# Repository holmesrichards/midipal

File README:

Midipal, the MIDI swiss army knife.

A midi in, a midi out, a small display, an encoder ; 20 awesome features:

* MIDI monitor
* BPM counter
* Keyboard splitter
* Note dispatcher / voice stealing / polyphonic driver
* Channels merger
* Channel filter
* Clock divider
* Clock source, with swing
* CC and NRPN knob
* 8 pots/sensors voltage reader/controller
* Drum pattern generator (including Euclidian patterns)
* Note, velocity and CC randomizer
* Chord memory
* Arpeggiator
* Sequencer
* CC lfo
* Tempo-synchronized note delay (with transposition and decay velocity)
* Slave start/stop synchronizer (à la Mungo Sync)
* Scale processor / harmonizer
* Ear training game

Forked from pichenettes' version and identical except:
- Eagle brd and sch files converted to XML (making possible import into KiCad)

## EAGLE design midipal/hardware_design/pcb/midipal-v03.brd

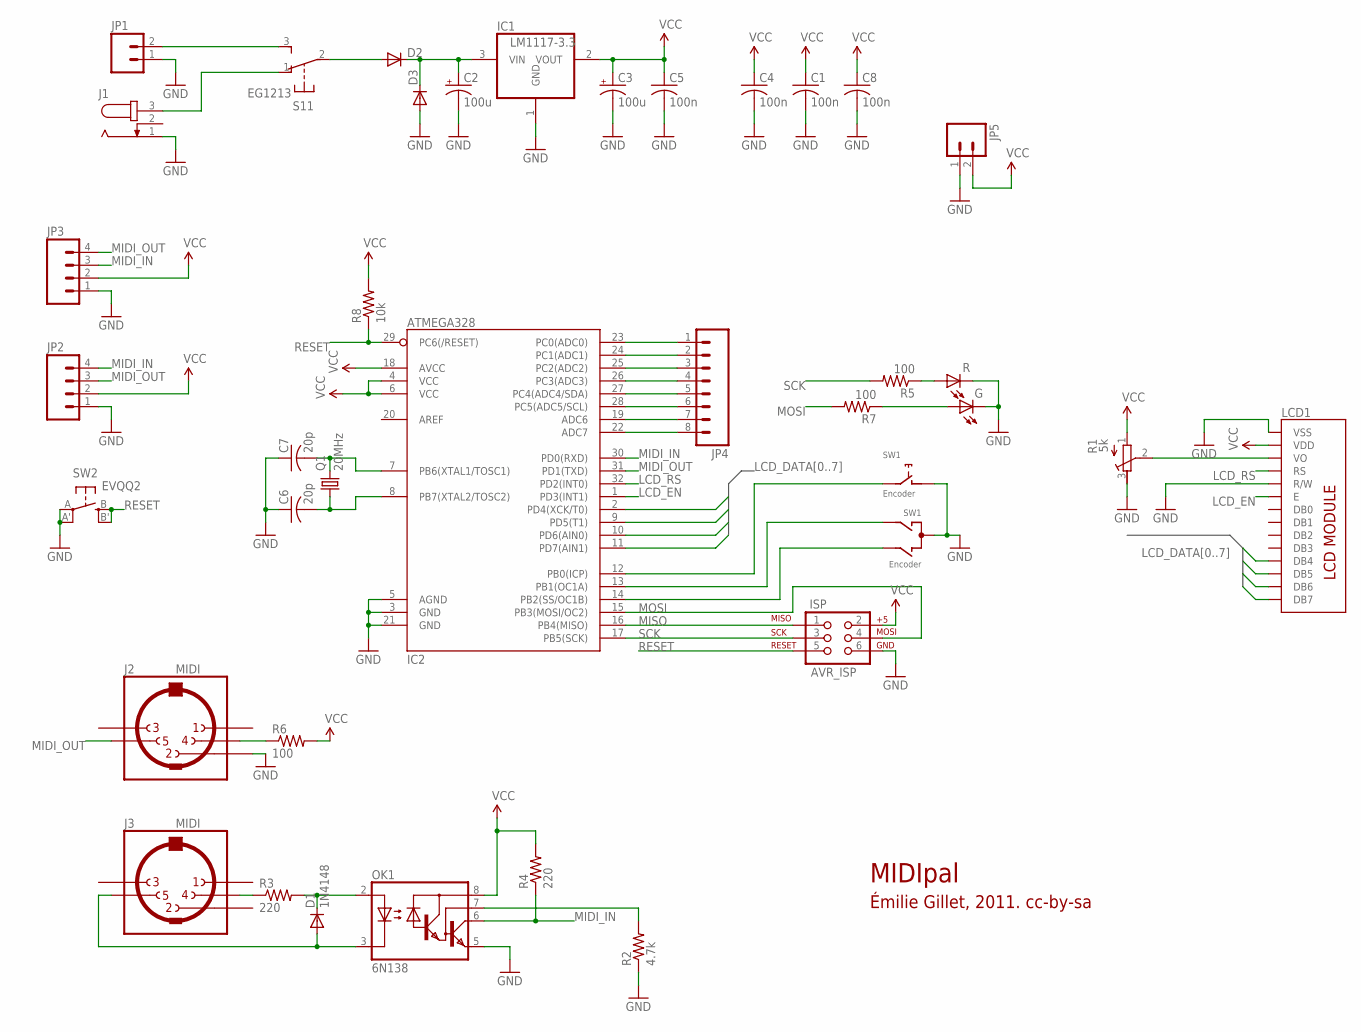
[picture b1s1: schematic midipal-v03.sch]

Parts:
C1, C4, C5, C8: 100n; C0805
C2, C3: 100u; PANASONIC_D
C6, C7: 20p; C0805
D1: 1N4148; SOD323-W
D2, D3: DIODESMB; SMB-DIODE
G: LEDCHIPLED_1206; CHIPLED_1206
IC1: LM1117-3.3; SOT223
IC2: ATMEGA328; TQFP32-08
ISP: AVR_ISP; 2X3
J1: JACK-PLUG2; SPC4078_BIG_HOLES
J2, J3: MIDI; MAB5SH
JP1: M02; 1X02_LONGPADS
JP2, JP3: M04PTH; 1X04
JP4: M08; 1X08
JP5: M02PTH; 1X02
LCD1: LCD_MODULE_NO_BKL; LCD_MODULE_1X8
OK1: 6N138; DIL8-SMD
Q1: 20MHz; HC49UP
R: LEDCHIPLED_1206; CHIPLED_1206
R1: 5k; RTRIM3296P
R2: 4.7k; M0805
R3: 220; M0805
R4: 220; R0805
R5, R6, R7: 100; R0805
R8: 10k; R0805
S1: EG1213
SW1: Encoder; ALPS_EC12E_SW
SW2: EVQQ2; EVQ-Q2

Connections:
GND: C1.2, C2.-, C3.-, C4.2, C5.2, C6.1, C7.1, C8.2, D3.A, G.C, IC1.1 (GND), IC2.3 (GND), IC2.5 (AGND), IC2.21 (GND), ISP.6, J1.1, J2.2, JP1.1, JP2.1, JP3.1, JP5.1, LCD1.1 (VSS), LCD1.5 (R/W), OK1.5 (GND), R.C, R1.3 (A), R2.1, SW1.C, SW1.D (1), SW2.A, SW2.A' (P1)
LCD_DATA4: IC2.2 (PD4(XCK/T0)), LCD1.11 (DB4)
LCD_DATA5: IC2.9 (PD5(T1)), LCD1.12 (DB5)
LCD_DATA6: IC2.10 (PD6(AIN0)), LCD1.13 (DB6)
LCD_DATA7: IC2.11 (PD7(AIN1)), LCD1.14 (DB7)
LCD_EN: IC2.1 (PD3(INT1)), LCD1.6 (E)
LCD_RS: IC2.32 (PD2(INT0)), LCD1.4 (RS)
MIDI_IN: IC2.30 (PD0(RXD)), JP2.4, JP3.3, OK1.6 (VO), R4.1
MIDI_OUT: IC2.31 (PD1(TXD)), J2.5, JP2.3, JP3.4
MISO: IC2.16 (PB4(MISO)), ISP.1
MOSI: IC2.15 (PB3(MOSI/OC2)), ISP.4, R7.2
unnamed: J1.3, S1.1 (O)
unnamed: C2.+, D2.C, D3.C, IC1.3 (VIN)
unnamed: IC2.23 (PC0(ADC0)), JP4.1
unnamed: D2.A, S1.2
unnamed: IC2.24 (PC1(ADC1)), JP4.2
unnamed: IC2.25 (PC2(ADC2)), JP4.3
unnamed: IC2.26 (PC3(ADC3)), JP4.4
unnamed: IC2.27 (PC4(ADC4/SDA)), JP4.5
unnamed: IC2.28 (PC5(ADC5/SCL)), JP4.6
unnamed: IC2.19 (ADC6), JP4.7
unnamed: IC2.22 (ADC7), JP4.8
unnamed: G.A, R7.1
unnamed: OK1.7 (VB), R2.2
unnamed: R.A, R5.1
unnamed: IC2.14 (PB2(SS/OC1B)), SW1.B
unnamed: IC2.13 (PB1(OC1A)), SW1.A
unnamed: IC2.12 (PB0(ICP)), SW1.E (2)
unnamed: LCD1.3 (VO), R1.2 (S)
unnamed: D1.C, OK1.2 (A), R3.2
unnamed: J2.4, R6.1
unnamed: J3.4, R3.1
unnamed: D1.A, J3.5, OK1.3 (C)
unnamed: C6.2, IC2.8 (PB7(XTAL2/TOSC2)), Q1.1
unnamed: C7.2, IC2.7 (PB6(XTAL1/TOSC1)), Q1.2
RESET: IC2.29 (PC6(/RESET)), ISP.5, R8.1, SW2.B (S), SW2.B' (S1)
SCK: IC2.17 (PB5(SCK)), ISP.3, R5.2
VCC: C1.1, C3.+, C4.1, C5.1, C8.1, IC1.2 (VOUT), IC2.4 (VCC), IC2.6 (VCC), IC2.18 (AVCC), ISP.2, JP2.2, JP3.2, JP5.2, LCD1.2 (VDD), OK1.8 (VCC), R1.1 (E), R4.2, R6.2, R8.2
VIN: JP1.2, S1.3 (S)

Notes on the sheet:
MIDIpal
Émilie Gillet, 2011. cc-by-sa

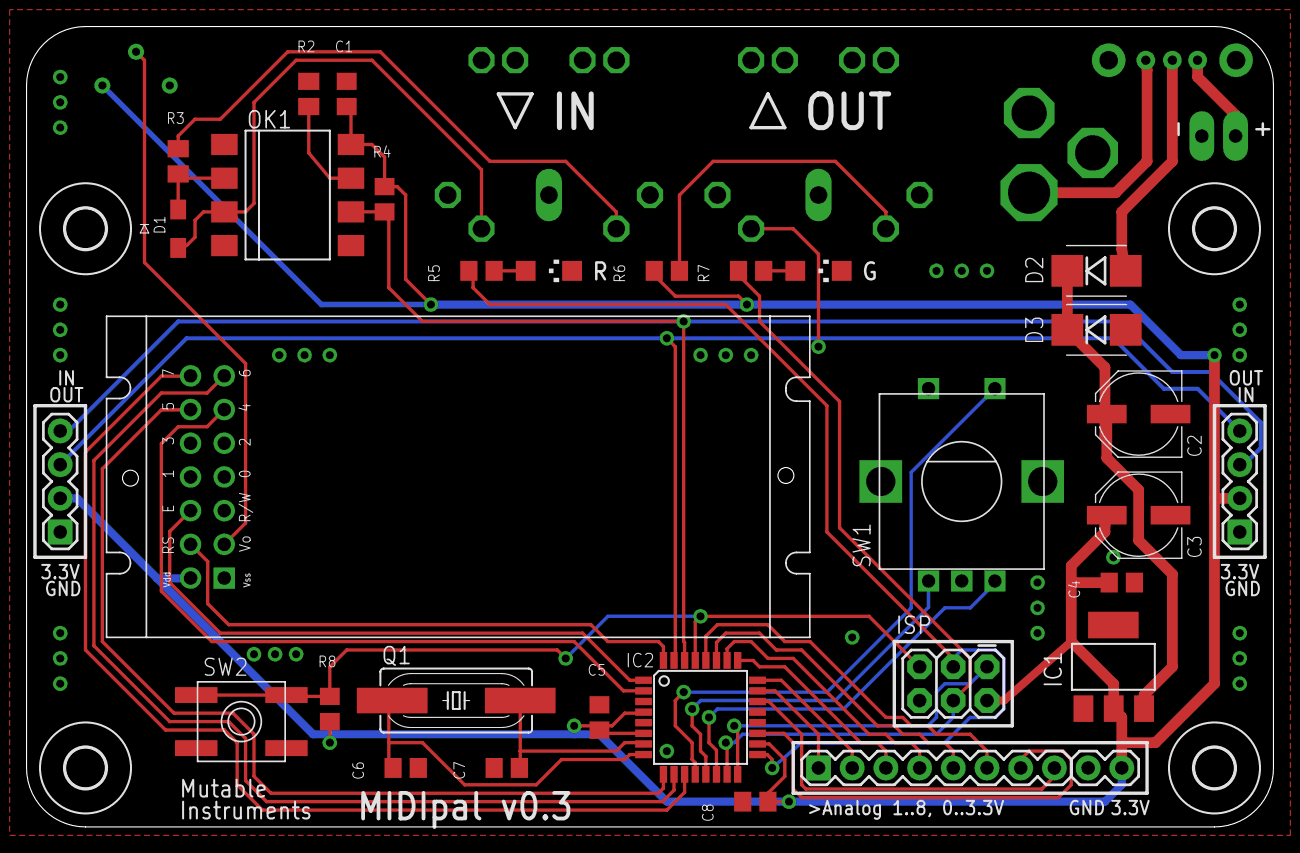
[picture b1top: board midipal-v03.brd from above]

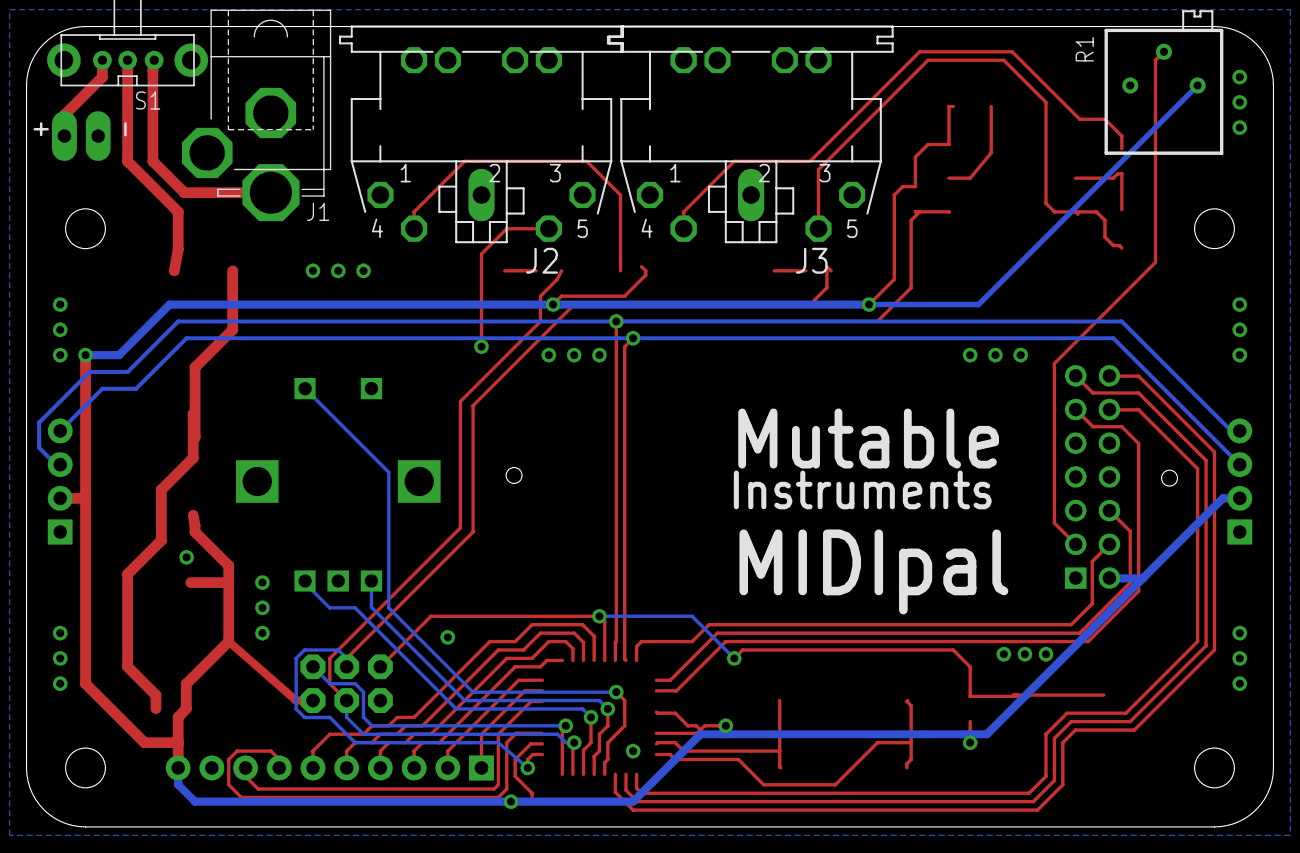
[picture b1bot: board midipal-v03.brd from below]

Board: 2 copper layers, 94.0 x 60.3 mm, 43 parts (6 on the bottom side), 39 nets.

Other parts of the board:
U$1, U$2, U$4, U$5: 3,0
U$3: SARASWATI

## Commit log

2020-03-23 Updated README for fork; XML conversions
